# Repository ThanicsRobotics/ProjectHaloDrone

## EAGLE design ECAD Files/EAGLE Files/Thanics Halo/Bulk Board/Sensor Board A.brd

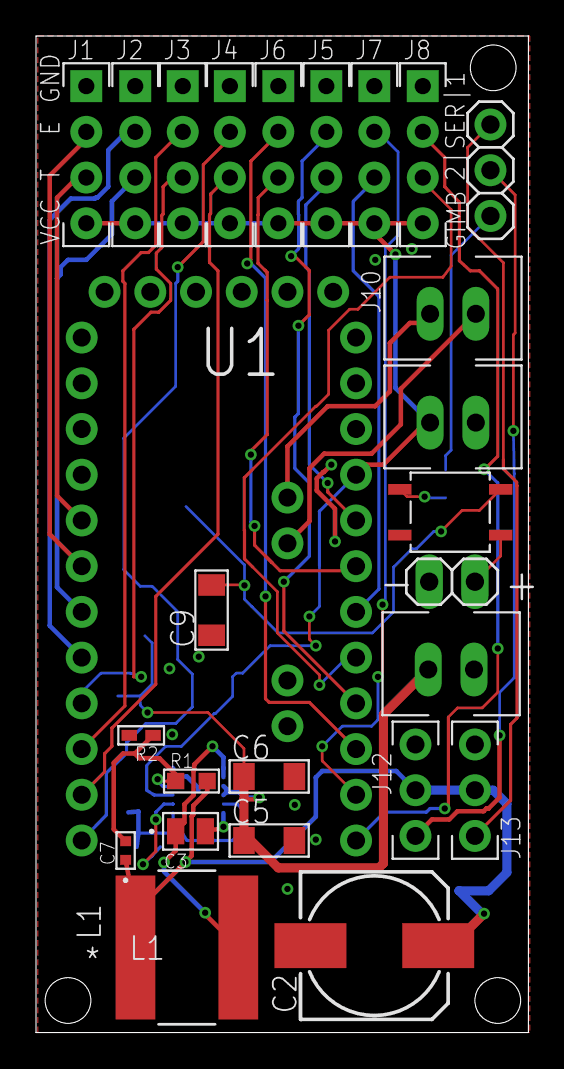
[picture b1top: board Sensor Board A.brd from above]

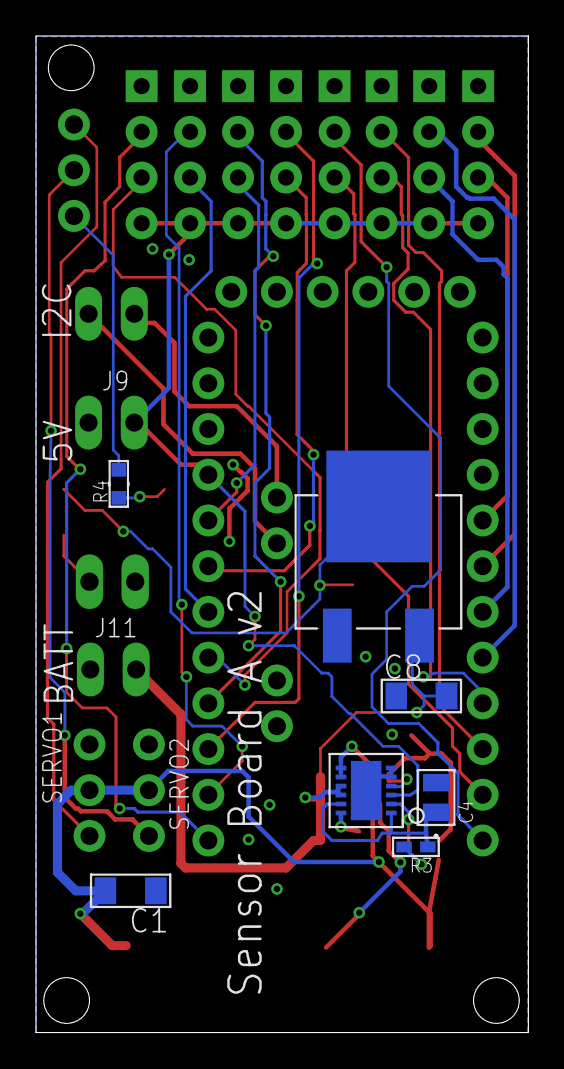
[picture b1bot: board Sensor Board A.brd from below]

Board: 2 copper layers, 27.4 x 55.4 mm, 33 parts (7 on the bottom side), 33 nets.

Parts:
C1, C5, C6, C8, C9: 10uF; 1206_MLCC
C2: 100uF; 0810_POLCAP
C3, C4: 0.1uF; 0805
C7: 16pF; G-155-M
J1, J2, J3, J4, J5, J6, J7, J8: HC-SR04; HC-SR04_FOOTPRINT
J9: POWER_CONNECTOR; XH_CONNECTOR
J10: I2C_CONNECTOR; XH_CONNECTOR
J11: GIMBAL_POWER_CONNECTOR; XH_CONNECTOR
J12, J13: SERVO_CONNECTOR
JP1: 1X03
JP2: 1X02
L1: 3.3uH; IND_BOURNS_SRN8040
R1: 499k; RC0603N-M
R2, R3: 95.3k; RC0402N-M
R4: 340R; RC0603N
U1: PRO-MINI-2
U2: 12LD4X3DFN
U3: 4-SOP
U4: DPAK

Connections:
+5V: J1.VCC, J2.VCC, J3.VCC, J4.VCC, J5.VCC, J6.VCC, J7.VCC, J8.VCC, J9.1, U1.VCC, U2.3
+12V: C9.P$2, U3.4, U4.2
ECHO1: J1.ECHO, U1.D3
ECHO2: J2.ECHO, U1.D5
ECHO3: J3.ECHO, U1.D7
ECHO4: J4.ECHO, U1.D9
ECHO5: J5.ECHO, U1.D13
ECHO6: J6.ECHO, U1.D12
ECHO7: J7.ECHO, U1.D11
ECHO8: J8.ECHO, U1.D10
GIMBAL: JP1.3, R4.2
GND: C1.P$1, C2.-, C4.2, C5.P$2, C6.P$2, C8.P$1, C9.P$1, J1.GND, J2.GND, J3.GND, J4.GND, J5.GND, J6.GND, J7.GND, J8.GND, J9.2, J11.2, J12.3, J13.3, JP2.2, R2.2, U1.GND, U1.GND1, U2.5, U2.6, U2.EP, U3.2, U4.1
unnamed: R4.1, U3.1
unnamed: R3.2, U2.2
unnamed: JP2.1, U3.3
unnamed: C7.2, R1.1, R2.1, U2.4
unnamed: C3.2, U2.12
unnamed: C3.1, L1.2, U2.7, U2.8
SCL: J10.1, U1.A5
SDA: J10.2, U1.A4
SERVO1: J12.1, JP1.1
SERVO2: J13.1, JP1.2
TRIG1: J1.TRIG, U1.D2
TRIG2: J2.TRIG, U1.D4
TRIG3: J3.TRIG, U1.D6
TRIG4: J4.TRIG, U1.D8
TRIG5: J5.TRIG, U1.A0
TRIG6: J6.TRIG, U1.A1
TRIG7: J7.TRIG, U1.A2
TRIG8: J8.TRIG, U1.A3
VDD: C4.1, R3.1, U2.1, U2.11
VOUT: C1.P$2, C2.+, C7.1, J12.2, J13.2, L1.1, R1.2
V_BATT: C5.P$1, C6.P$1, C8.P$2, J11.1, U2.9, U2.10, U4.3

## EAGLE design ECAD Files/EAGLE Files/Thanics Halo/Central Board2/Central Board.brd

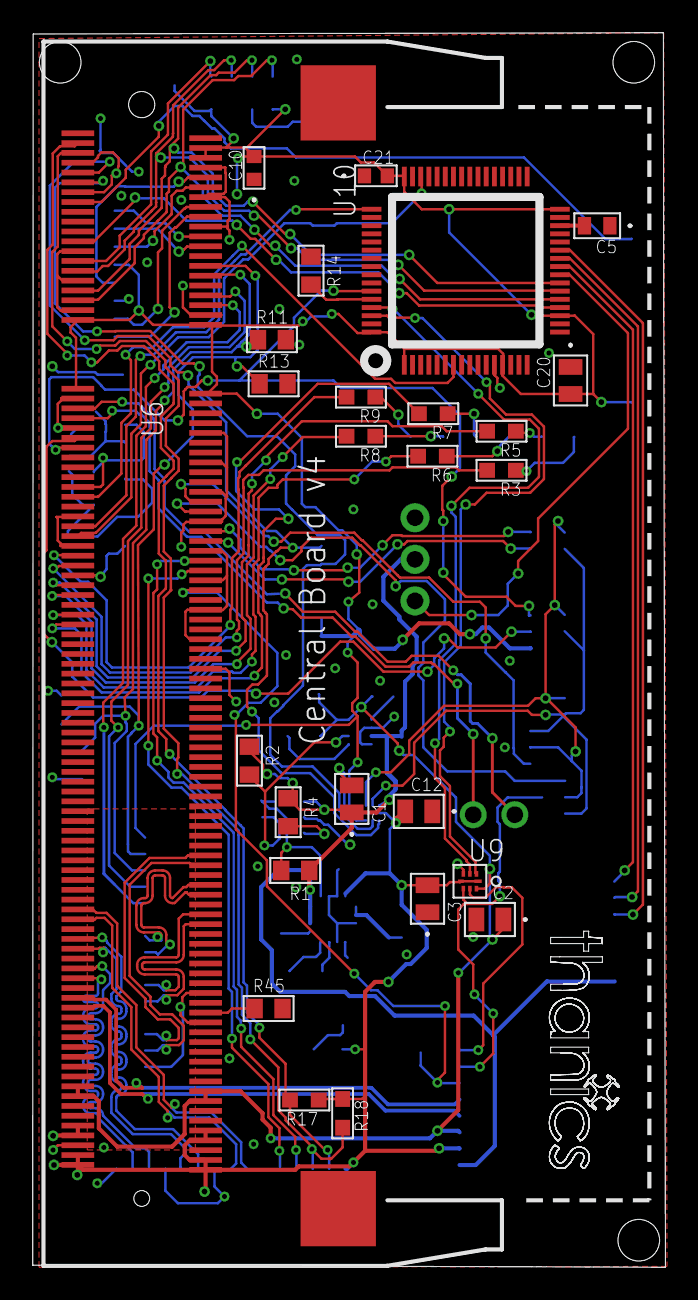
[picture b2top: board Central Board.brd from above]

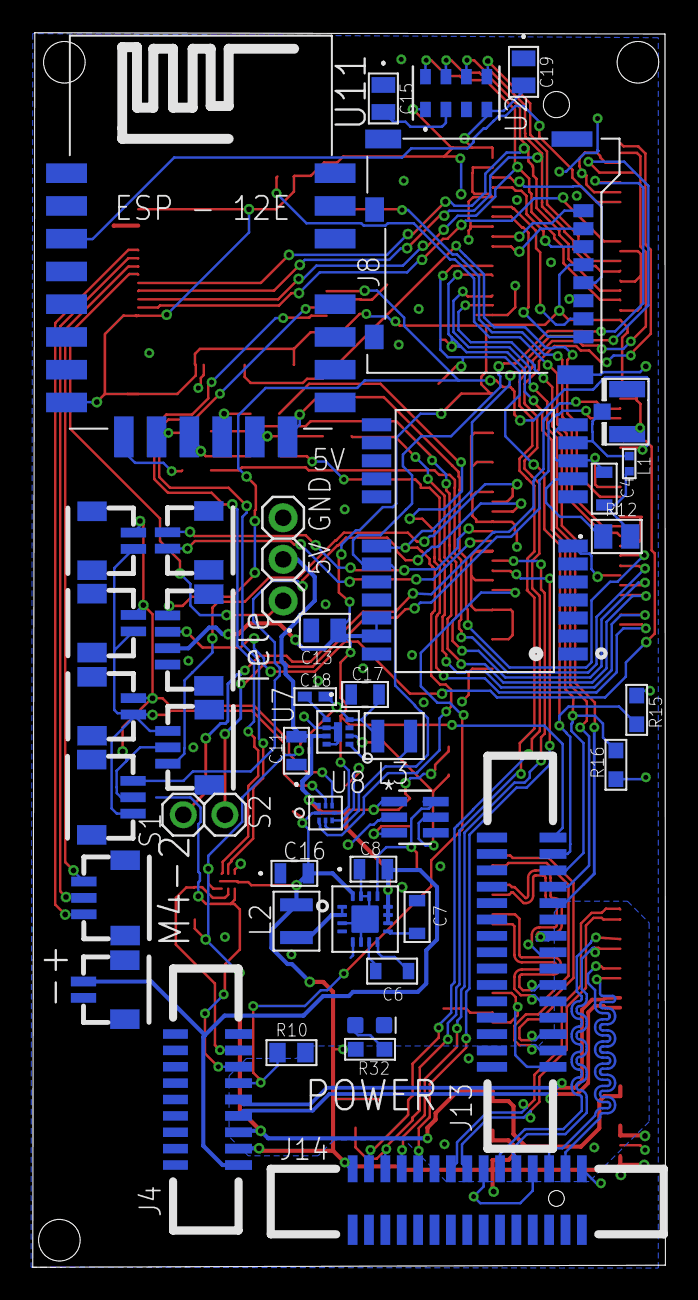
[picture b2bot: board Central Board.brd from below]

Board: 4 copper layers, 38.6 x 75.4 mm, 69 parts (43 on the bottom side), 91 nets.

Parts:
C1, C2, C3, C12, C13, C20: 0.1uF; 0805
C4, C6, C7: 10nF; 0603_CAPACITOR
C5: 4.7uF; 0603-M
C8, C11, C17: 10uF; G-21
C10, C21: 2.2uF; G-188-M
C15, C19: 1uF; YAG_CC0805
C16: 22uF; G-21
C18: 560pF; CC0402N-M
D1: GREEN; LED-0603
J1, J2, J6, J7, J9: JST_SH_2POS
J3: JST_SH_4POS
J4: 9POS_FFC_CONNECTOR
J5: U.FL
J8: MICROSD
J10, J11, J12: JST_SH_3POS
J13, J14: 15POS_FFC_CONNECTOR
JP1: 1X02
JP2: 1X03
L1: 27 nH; 0402_INDUCTOR
L2, L3: 470nH; 1008_INDUCTOR
R1, R2, R4, R10, R11, R13, R14, R45: 10k; RC0805N
R3, R5, R6, R7, R8, R9, R32: 20R; RC0603N-M
R12: 10; STA_RNCP0805-M
R15, R16, R17, R18: 1k; RC0603N-M
U2: LGA8-M
U3: LM3880MF-1AA/NOPBMF06A-M; MF06A-M
U4: NEO-M8
U5: TPS6209; VQFN16
U6: SO-DIMM
U7: MIC23050; MLF(ML)_8PIN
U8, U9: 8-UMLP
U10: LQFP64
U11: ESP12E-SMD

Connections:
1.8V: C2.1, C17.2, C18.2, J4.3, L3.P$2, U6.183, U6.184, U6.185, U6.186, U7.4, U9.8
+3V3: C3.2, C10.2, C12.2, C13.2, C16.2, C19.2, C20.2, C21.2, J3.3, J4.2, J8.4, J13.15, J14.15, L2.P$2, R15.1, R16.1, R17.1, R18.1, R32.2, U2.1, U2.4, U4.22, U4.23, U5.16, U6.4, U6.6, U6.39, U6.40, U6.41, U6.42, U6.191, U6.192, U6.193, U6.194, U6.197, U6.198, U6.199, U6.200, U8.1, U8.5, U9.1, U9.5, U10.1, U10.13, U10.19, U10.32, U10.48, U10.64, U11.VCC
+5V: C1.1, C8.2, C11.2, J4.1, J6.1, JP2.2, R1.1, R2.1, R4.1, U3.1, U5.10, U5.11, U5.12, U7.7, U8.8
C0_C_N: J13.8, U6.144
C0_C_P: J13.9, U6.142
C0_D0_N: J13.2, U6.138
C0_D0_P: J13.3, U6.136
C0_D1_N: J13.5, U6.150
C0_D1_P: J13.6, U6.148
C0_IO0: J13.11, U6.36
C0_IO1: J13.12, U6.34
C1_C_N: J14.8, U6.149
C1_C_P: J14.9, U6.147
C1_D0_N: J14.2, U6.161
C1_D0_P: J14.3, U6.159
C1_D1_N: J14.5, U6.155
C1_D1_P: J14.6, U6.153
C1_IO0: J14.11, U6.78
C1_IO1: J14.12, U6.76
GND: C1.2, C2.2, C3.1, C4.1, C5.1, C7.1, C8.1, C10.1, C11.1, C12.1, C13.1, C15.1, C16.1, C17.1, C19.1, C20.1, C21.1, D1.C, J3.4, J4.9, J5.P$1, J5.P$2, J6.2, J8.6, J8.9, J8.10, J8.11, J8.12, J8.13, J13.1, J13.4, J13.7, J13.10, J14.1, J14.4, J14.7, J14.10, JP2.3, R10.2, R11.2, R13.2, R14.1, R45.2, U2.3, U3.2, U4.7, U4.10, U4.12, U4.13, U4.24, U5.3, U5.5, U5.6, U5.14, U5.15, U5.17, U6.1, U6.7, U6.8, U6.13, U6.14, U6.19, U6.20, U6.25, U6.26, U6.31, U6.32, U6.37, U6.38, U6.43, U6.44, U6.49, U6.50, U6.55, U6.56, U6.61, U6.62, U6.67, U6.68, U6.73, U6.74, U6.79, U6.80, U6.85, U6.86, U6.91, U6.92, U6.97, U6.98, U6.103, U6.104, U6.109, U6.110, U6.115, U6.116, U6.121, U6.122, U6.127, U6.133, U6.134, U6.139, U6.140, U6.145, U6.146, U6.151, U6.152, U6.157, U6.163, U6.164, U6.169, U6.170, U6.181, U6.182, U6.187, U6.188, U6.195, U6.196, U6.G1, U6.G2, U7.6, U7.8, U7.EP, U8.4, U9.4, U10.12, U10.18, U10.31, U10.47, U10.63, U11.GND
GPCLK1: J4.6, R10.1, U6.82
I2C_MPU_SCL: U9.3, U10.61
I2C_MPU_SDA: U9.2, U10.62
I2C_SCL: U4.19, U6.11, U8.3
I2C_SCL_1V8: J4.7, U9.6
I2C_SCL_5V: J1.2, J2.2, J7.2, J10.2, J11.2, U8.6
I2C_SDA: U4.18, U6.9, U8.2
I2C_SDA_1V8: J4.8, U9.7
I2C_SDA_5V: J1.1, J2.1, J7.1, J10.1, J11.1, U8.7
ID_SD: U6.15, U11.CH_PD
INT_A: J10.3, U6.64
INT_B: J11.3, U6.66
MOTOR1: JP2.1, U10.24
MOTOR2: J12.1, U10.25
MOTOR3: J12.2, U10.26
MOTOR4: J12.3, U10.27
unnamed: J5.P$3, L1.P$1, U4.11
unnamed: C6.2, U5.7
unnamed: C6.1, U5.8
unnamed: D1.A, R32.1
unnamed: R1.2, U3.6, U5.13
unnamed: R2.2, U3.5, U7.2
unnamed: R3.1, U11.CS0
unnamed: R5.1, U11.MISO
unnamed: R6.1, U11.GPIO9
unnamed: R7.1, U11.GPIO10
unnamed: C5.2, U10.30
unnamed: C15.2, U2.2
unnamed: R12.1, U4.9
unnamed: R8.1, U11.MOSI
unnamed: R9.1, U11.SCLK
unnamed: R14.2, U10.60
unnamed: C4.2, L1.P$2, R12.2
unnamed: C7.2, U5.9
unnamed: L2.P$1, U5.1, U5.2
unnamed: L3.P$1, U7.1
unnamed: C18.1, U7.5
unnamed: R45.1, U6.168
NRST: U6.63, U10.7
POWER_SEQ_EN: R4.2, U3.3
SCL0: J13.13, R11.1, R16.2, U6.30
SCL1: J14.13, R18.2, U6.5
SDA0: J13.14, R13.1, R15.2, U6.28
SDA1: J14.14, R17.2, U6.3
SDX_CLK: J8.5, U6.10
SDX_CMD: J8.3, U6.12
SDX_D0: J8.7, U6.16
SDX_D1: J8.8, U6.18
SDX_D2: J8.1, U6.22
SDX_D3: J8.2, U6.24
SD_CLK: R9.2, U6.75
SD_CMD: R3.2, U6.77
SD_D0: R5.2, U6.81
SD_D1: R8.2, U6.83
SD_D2: R6.2, U6.87
SD_D3: R7.2, U6.89
SERVO1: JP1.1, U6.45
SERVO2: JP1.2, U6.47
SPI_CS0: U2.5, U6.27
SPI_CS1: U6.23, U10.20
SPI_MISO: U2.6, U6.29, U10.22
SPI_MOSI: U2.7, U6.33, U10.23
SPI_SCLK: U2.8, U6.35, U10.21
SWCLK: U6.69, U10.49
SWDIO: U6.71, U10.46
UART2_RX: J9.2, U6.72
UART2_TX: J9.1, U6.70
USART1_RX: J3.1, U6.53, U10.59
USART1_TX: J3.2, U6.51
USB_D_N: J4.4, U6.167
USB_D_P: J4.5, U6.165

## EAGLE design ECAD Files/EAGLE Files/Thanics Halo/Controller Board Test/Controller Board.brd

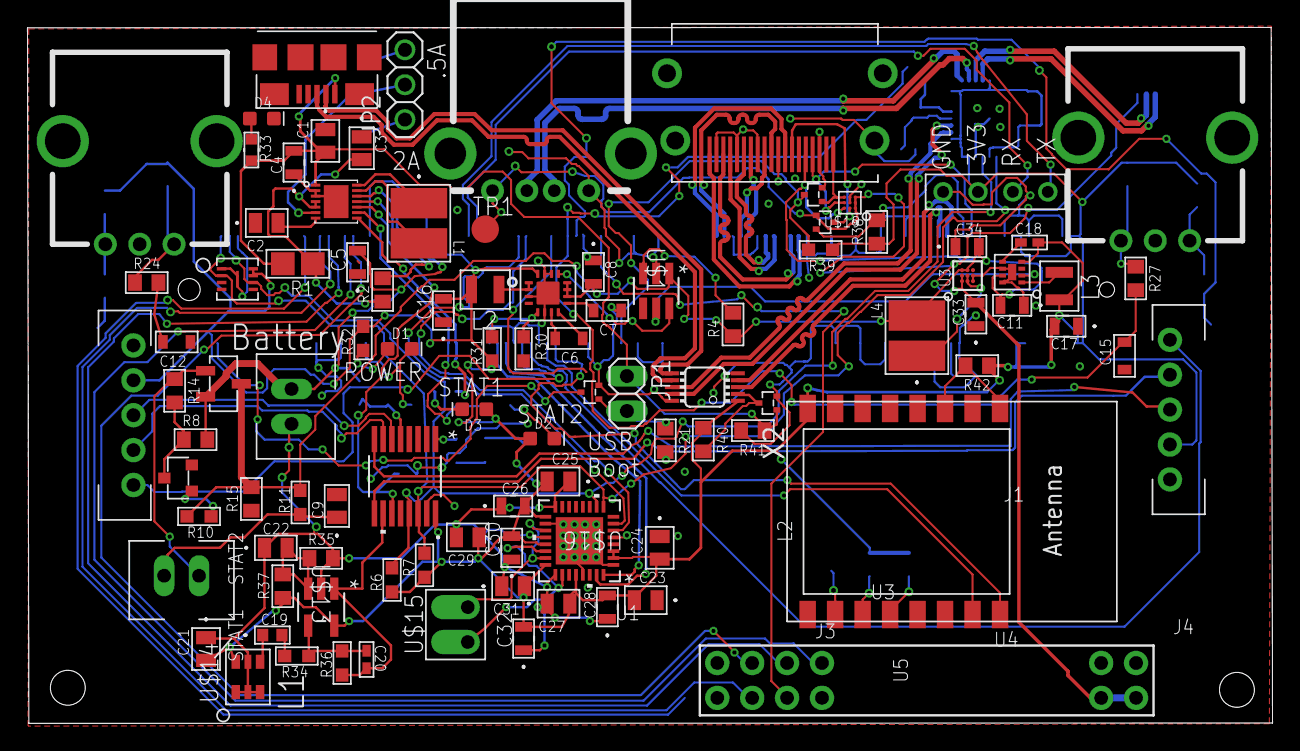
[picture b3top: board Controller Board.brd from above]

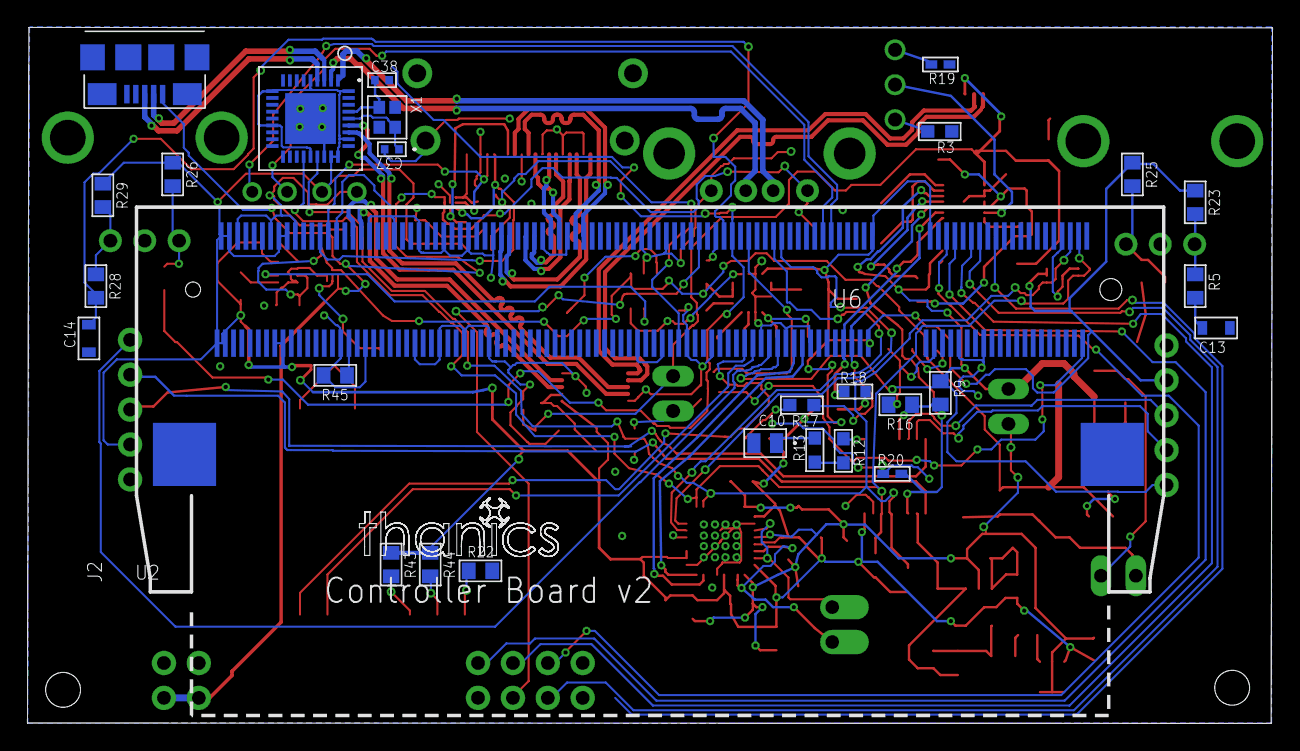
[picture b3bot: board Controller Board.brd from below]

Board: 2 copper layers, 90.6 x 50.6 mm, 128 parts (28 on the bottom side), 113 nets.

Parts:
C1, C2, C10, C21, C23, C24, C25, C27, C29, C31: 0.1uF; 0805
C3, C9, C22: 1uF; YAG_CC0805
C4, C8, C11, C17, C26, C28, C33, C34: 10uF; G-21
C5, C16, C30, C32: 22uF; G-21
C6, C7, C12, C13, C14, C15: 10nF; 0603_CAPACITOR
C18, C20: 560pF; CC0402N-M
C19: 2.2uF; G-188-M
C37, C38: 16pF; G-155-M
D1, D2, D3, D4: GREEN; LED-0603
IC1: FSUSB42MSOP10; MSOP10
J1, J2: JOYSTICK; JST-XH_5POS
J3, J5: USB_MICRO_B_SMT
J4: 2_PIN_CONNECTOR; XH_CONNECTOR
J6: POWER_CONNECTOR; XH_CONNECTOR
J7: HDMI
JP1: 1X02
JP2: 1X03
L1, L4: 4.7uH; IND_IFSC_1515AH-M
L2, L3: 470nH; 470NH_INDUCTOR
R1: 100; 1206
R2, R4, R5, R8, R9, R14, R15, R16, R21, R22, R23, R24, R25, R26, R27, R28, R29, R35, R37, R40, R41, R42, R43, R44, R45: 10k; RC0805N
R3, R10, R36, R39: 100k; RC0603N-M
R6, R7, R12, R13, R34: 1k; RC0603N-M
R11: 1M; RC0603N-M
R17, R32: 20R; RC0603N-M
R18, R33: 340R; RC0603N
R19, R20: 24.9k; RC0402N-M
R30: 160k; RC0603N-M
R31: 499k; RC0603N-M
R38: NF; RC0805N
TP1: TPSQTP20R; TP20R
U1: AAT3620_BATT_CHARGER; AAT3620_TDFN
U2: 8 CH; 21-0055H_16-M
U3: YFF9
U4: DMP3030SN_MOSFET; SC59_MOSFET
U5: SOT-23_(TO-236AB)
U6: COMPUTE_MODULE; SO-DIMM
U$1: LM3880MF-1AA/NOPBMF06A-M; MF06A-M
U$2: APPLE_2.0C_COPROCESSOR; PG-USON-8-1
U$3: 4_PIN_TELE_CONNECTOR
U$4: MIC23050; MLF(ML)_8PIN
U$5: TPS6209; VQFN16
U$9, U$10: PEC12R
U$11: USB_A_RECEPT
U$12: 3.5_TOUCHSCREEN
U$13: SOT-23-5_MC-M
U$14: SISONIC_MICROPHONE
U$15: SPEAKER
U$16: RHB32_3P45X3P45
U$18, U$20, U$21, U$23: SOT-523
U$19: ESD5384; WLCSP9
U$24: 36-SQFN
U$25: AGND-DGND
X1: 24MHZ; FA-128
X2: ESP-12

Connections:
+3V3: C16.2, C17.2, C18.2, C21.2, C23.2, C24.2, C25.2, C26.2, C27.2, C28.2, C29.2, C30.2, C31.2, C32.2, D2.A, D3.A, IC1.1, J1.2, J2.2, L2.P$2, L3.P$2, R6.1, R7.1, R23.1, R25.1, R26.1, R29.1, R31.1, R32.2, R37.1, R38.1, R39.1, R40.1, R42.1, R43.1, R44.1, U2.16, U6.39, U6.40, U6.41, U6.42, U6.183, U6.184, U6.185, U6.186, U6.197, U6.198, U6.199, U6.200, U$2.7, U$2.8, U$3.3, U$4.4, U$5.16, U$13.5, U$14.6, U$16.2, U$16.3, U$16.17, U$16.21, U$16.24, U$16.28, U$24.5, U$24.10, U$24.15, U$24.23, U$24.26, U$24.27, U$24.29, U$24.36, X2.8
+5V: C33.2, J5.1, TP1.TP, U3.A1, U3.A2, U$11.1, U$12.1, U$12.2, U$18.G, U$19.A1, U$19.B1, U$19.C1
AGND: C21.1, C22.1, C25.1, C26.1, C27.1, C28.1, C29.1, C30.1, C31.1, C32.1, R35.2, U$13.2, U$14.1, U$14.2, U$14.3, U$14.5, U$16.16, U$16.20, U$16.25, U$25.1
D1_N: IC1.6, J3.2
D1_P: IC1.7, J3.3
D2_N: IC1.8, U$24.30
D2_P: IC1.9, U$24.31
DS1_N: U$11.2, U$24.1
DS1_P: U$11.3, U$24.2
DS2_N: J5.2, U$24.3
DS2_P: J5.3, U$24.4
EMMC_DISABLE_N: U6.2, U$20.D
ENCODER1_A: C13.2, R5.2, U6.76
ENCODER1_B: C12.2, R24.2, U6.78
ENCODER2_A: C15.2, R27.2, U6.75
ENCODER2_B: C14.2, R28.2, U6.77
GND: C1.1, C2.1, C3.1, C4.1, C5.1, C7.1, C8.1, C9.2, C10.2, C11.1, C12.1, C13.1, C14.1, C15.1, C16.1, C17.1, C23.1, C24.1, C33.1, C34.1, C37.2, C38.2, D1.C, D4.C, IC1.5, IC1.10, J1.1, J2.1, J3.4, J3.5, J3.6, J3.7, J3.P$1, J3.P$2, J3.P$3, J3.P$4, J5.4, J5.5, J5.6, J5.7, J5.P$1, J5.P$2, J5.P$3, J5.P$4, J6.2, J7.2, J7.5, J7.8, J7.11, J7.17, J7.P$1, J7.P$2, J7.P$3, J7.P$4, R3.1, R15.1, R16.2, R19.1, R20.1, R21.2, R22.2, R30.2, R41.2, R45.2, U1.2, U1.3, U1.EP, U2.15, U3.C1, U3.C2, U5.S, U6.1, U6.7, U6.8, U6.13, U6.14, U6.19, U6.20, U6.25, U6.26, U6.31, U6.32, U6.37, U6.38, U6.43, U6.44, U6.49, U6.50, U6.55, U6.56, U6.61, U6.62, U6.67, U6.68, U6.73, U6.74, U6.79, U6.80, U6.85, U6.86, U6.91, U6.92, U6.97, U6.98, U6.103, U6.104, U6.109, U6.110, U6.115, U6.116, U6.121, U6.122, U6.127, U6.133, U6.134, U6.139, U6.140, U6.145, U6.146, U6.151, U6.152, U6.157, U6.163, U6.164, U6.169, U6.170, U6.181, U6.182, U6.187, U6.188, U6.195, U6.196, U6.G1, U6.G2, U$1.2, U$2.1, U$2.9, U$3.4, U$4.6, U$4.8, U$4.EP, U$5.3, U$5.6, U$5.14, U$5.15, U$5.17, U$9.C, U$10.C, U$11.4, U$11.5, U$11.6, U$12.3, U$12.7, U$16.1, U$16.18, U$16.29, U$16.33, U$19.B2, U$19.C2, U$20.S, U$21.S, U$23.S, U$24.25, U$24.EP, U$25.2, X2.9
GPIO18: U6.63, U$16.7
GPIO19: U6.65, U$16.6
GPIO21: U6.71, U$16.5
GPIO25: U6.83, U$12.4
GPIO36: U6.58, U$16.32
GPIO37: U6.60, U$16.31
HDMI_CEC: R38.2, U6.171, U$18.S
HDMI_CK_N: J7.12, U6.111
HDMI_CK_P: J7.10, U6.113
HDMI_D0_N: J7.9, U6.117
HDMI_D0_P: J7.7, U6.119
HDMI_D1_N: J7.6, U6.123
HDMI_D1_P: J7.4, U6.125
HDMI_D2_N: J7.3, U6.129
HDMI_D2_P: J7.1, U6.131
HDMI_HPD_N_1V8: R39.2, U6.88, U$21.D
HDMI_SCL: J7.15, U6.175, U$19.A3
HDMI_SDA: J7.16, U6.173, U$19.B3
I2C_SCL: R6.2, U2.13, U6.5, U$2.6, U$16.10, U$24.24
I2C_SDA: R7.2, U2.14, U6.3, U$2.2, U$16.9, U$24.22
ISET: JP2.2, U1.6
ITERM: R20.2, U1.10, U2.11
J1_SW: J1.5, U6.64
J2_SW: J2.5, U6.66
MIC_OUTPUT: C20.2, R36.1, U2.10, U$13.1
unnamed: J4.1, R14.1, U4.G
unnamed: C2.2, U1.7
unnamed: JP1.2, R21.1, U$20.G
unnamed: L1.2, U1.13
unnamed: L1.1, U1.14
unnamed: C3.2, R1.1, R2.1, U1.4, U1.5
unnamed: C5.2, J6.1, R8.2, R9.1, U1.12, U4.S
unnamed: U$1.6, U$5.13
unnamed: D4.A, R33.1
unnamed: D1.A, R32.1
unnamed: R2.2, U1.11
unnamed: U$1.5, U$4.2
unnamed: C6.2, U$5.7
unnamed: C19.1, U$14.4
unnamed: D2.C, R17.2
unnamed: R12.1, U2.1
unnamed: J1.3, U2.6
unnamed: J1.4, U2.7
unnamed: J2.3, U2.8
unnamed: J2.4, U2.9
unnamed: C19.2, R34.2
unnamed: D3.C, R18.2
unnamed: C6.1, U$5.8
unnamed: R12.2, R13.1
unnamed: R10.1, U5.G
unnamed: C9.1, J4.2, R11.1
unnamed: R8.1, R14.2, U5.D
unnamed: C10.1, R13.2
unnamed: C7.2, U$5.9
unnamed: L2.P$1, U$5.1, U$5.2
unnamed: R5.1, R23.2, U$9.A
unnamed: L3.P$1, U$4.1
unnamed: R42.2, X2.1, X2.3
unnamed: R24.1, R25.2, U$9.B
unnamed: C20.1, R34.1, R36.2, U$13.4
unnamed: C22.2, R35.1, R37.2, U$13.3
unnamed: R26.2, R27.1, U$10.A
unnamed: R28.1, R29.2, U$10.B
unnamed: R9.2, R16.1, U2.5
unnamed: JP2.1, R3.2
unnamed: U$15.1, U$16.22, U$16.26
unnamed: JP2.3, R19.2
unnamed: R22.1, X2.10
unnamed: U$15.2, U$16.19, U$16.23
unnamed: R43.2, X2.12
unnamed: R30.1, R31.2, U$5.5
unnamed: C8.2, C11.2, C34.2, L4.2, R4.1, R10.2, R11.2, R15.2, U3.A3, U3.B3, U4.D, U$1.1, U$4.7, U$5.10, U$5.11, U$5.12
unnamed: C18.1, U$4.5
unnamed: J7.13, U$18.D, U$19.A2
unnamed: J7.19, U$19.C3, U$21.G
unnamed: R44.2, X2.11
unnamed: C38.1, U$24.33, X1.1
unnamed: R45.1, U6.168
unnamed: IC1.2, R40.2, U$23.D
unnamed: C37.1, U$24.32, X1.3
unnamed: L4.1, U3.B1, U3.B2
POWER_SEQ_EN: R4.2, U$1.3
SPI_CS0: U6.27, U$12.5
SPI_CS1: U6.23, U$12.6
SPI_MISO: U6.29, U$12.9
SPI_MOSI: U6.33, U$12.10
SPI_SCLK: U6.35, U$12.8
STAT1: R17.1, U1.9, U6.46
STAT2: R18.1, U1.8, U6.48
UART2_RX: U6.72, X2.16
UART2_TX: U6.70, X2.15
UART_RX: U6.53, U$3.2
UART_TX: U6.51, U$3.1
USB_5V: C1.2, C4.2, J3.1, JP1.1, R1.2, R33.2, R41.1, U1.1, U$23.G
USB_D_N: IC1.4, U6.167
USB_D_P: IC1.3, U6.165

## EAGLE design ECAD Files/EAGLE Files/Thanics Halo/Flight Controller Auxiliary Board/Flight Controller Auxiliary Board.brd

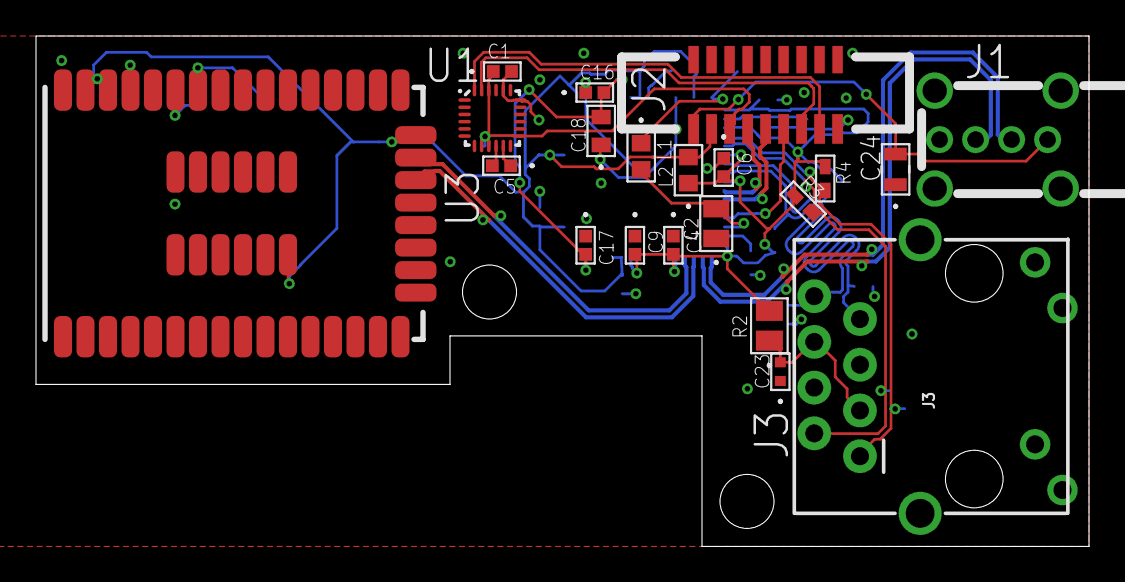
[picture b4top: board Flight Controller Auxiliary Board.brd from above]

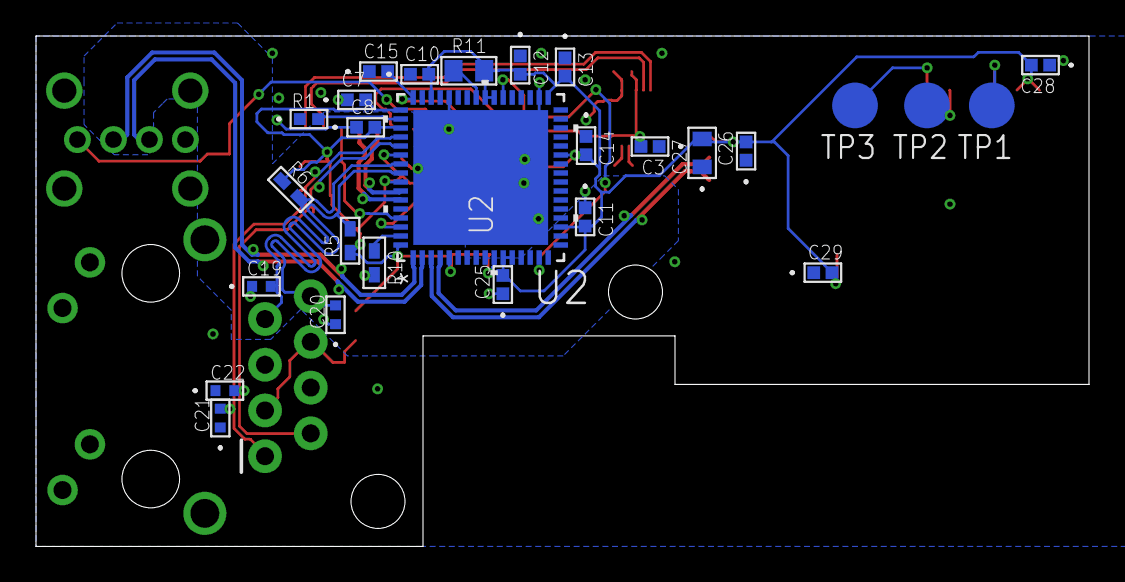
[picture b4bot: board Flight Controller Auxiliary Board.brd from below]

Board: 4 copper layers, 58.5 x 28.4 mm, 48 parts (27 on the bottom side), 29 nets.

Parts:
C1, C3, C4, C5, C6, C7, C8, C9, C10, C11, C12, C13, C14, C15, C16, C17, C25, C26, C28, C29: 0.1uF; 0402-M
C2: 1uF; YAG_CC0805
C18, C27: 4.7uF; 0603-M
C19, C20, C21, C22: 16pF; G-155-M
C23: 22nF; G-155-M
C24: 22uF; G-21
J1: USB_A_VERTICAL
J2: 9POS_FFC_CONNECTOR
J3: MAGJACK
L1, L2: FB; IND_BLM18_0603-M
R1: 12.4k; YAG_R0402-M
R2: 10R; STA_RNCP0805-M
R3, R4, R5, R6: 49R9; RC0402N-M
R10: 12k; RC0402N-M
R11: 10k; RC0805N
TP1, TP2, TP3: TPB2,54; B2,54
U1: QFN40P300X300X105-25N
U2: QFN64_9X9MC-M
U3: WGM110A

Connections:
1.8V: C1.1, C3.2, J2.3, U1.8, U1.9, U1.13, U1.22
3.3V_A: C4.2, C6.2, C7.2, C8.2, C9.2, L2.1, R2.2, R3.1, R4.1, R5.1, R6.1, U2.5, U2.10, U2.49, U2.51, U2.54, U2.57, U2.64
+3V3: C10.2, C11.2, C12.2, C13.2, C14.2, C25.2, C26.2, C27.2, C28.2, C29.2, J2.2, L2.2, R11.2, U2.11, U2.12, U2.19, U2.27, U2.33, U2.39, U2.40, U2.46, U3.24, U3.38, U3.39, U3.51
+5V: C24.2, J1.1, J2.1
GND: C1.2, C2.1, C3.1, C4.1, C5.1, C6.1, C7.1, C8.1, C9.1, C10.1, C11.1, C12.1, C13.1, C14.1, C15.1, C16.1, C17.1, C18.1, C19.1, C20.1, C21.1, C22.1, C23.1, C24.1, C25.1, C26.1, C27.1, C28.1, C29.1, J1.4, J1.P$5, J1.P$6, J1.P$7, J1.P$8, J2.9, J3.10, J3.12, J3.M1, J3.M2, R1.1, R10.2, U1.11, U1.18, U1.20, U2.34, U2.44, U2.65, U3.1, U3.16, U3.25, U3.40, U3.42, U3.44, U3.46, U3.48
GPCLK: J2.6, U2.61
unnamed: R11.1, U2.41
unnamed: R10.1, U2.63
unnamed: C15.2, L1.1, U2.48
unnamed: C2.2, L1.2, U2.62
unnamed: TP1.TP, U3.37
unnamed: TP2.TP, U3.35
unnamed: TP3.TP, U3.34
unnamed: C5.2, U1.10
unnamed: R1.2, U2.50
unnamed: C16.2, C17.2, C18.2, U2.15, U2.38
unnamed: C23.2, J3.3, J3.6, R2.1
RX_N: C22.2, J3.2, R3.2, U2.53
RX_P: C21.2, J3.1, R4.2, U2.52
SCL: J2.7, U1.23
SDA: J2.8, U1.24
TX_N: C20.2, J3.8, R5.2, U2.56
TX_P: C19.2, J3.7, R6.2, U2.55
USB_D2_N: J1.2, U2.1
USB_D2_P: J1.3, U2.2
USB_D3_N: U2.3, U3.22
USB_D3_P: U2.4, U3.23
USB_D_N: J2.4, U2.58
USB_D_P: J2.5, U2.59

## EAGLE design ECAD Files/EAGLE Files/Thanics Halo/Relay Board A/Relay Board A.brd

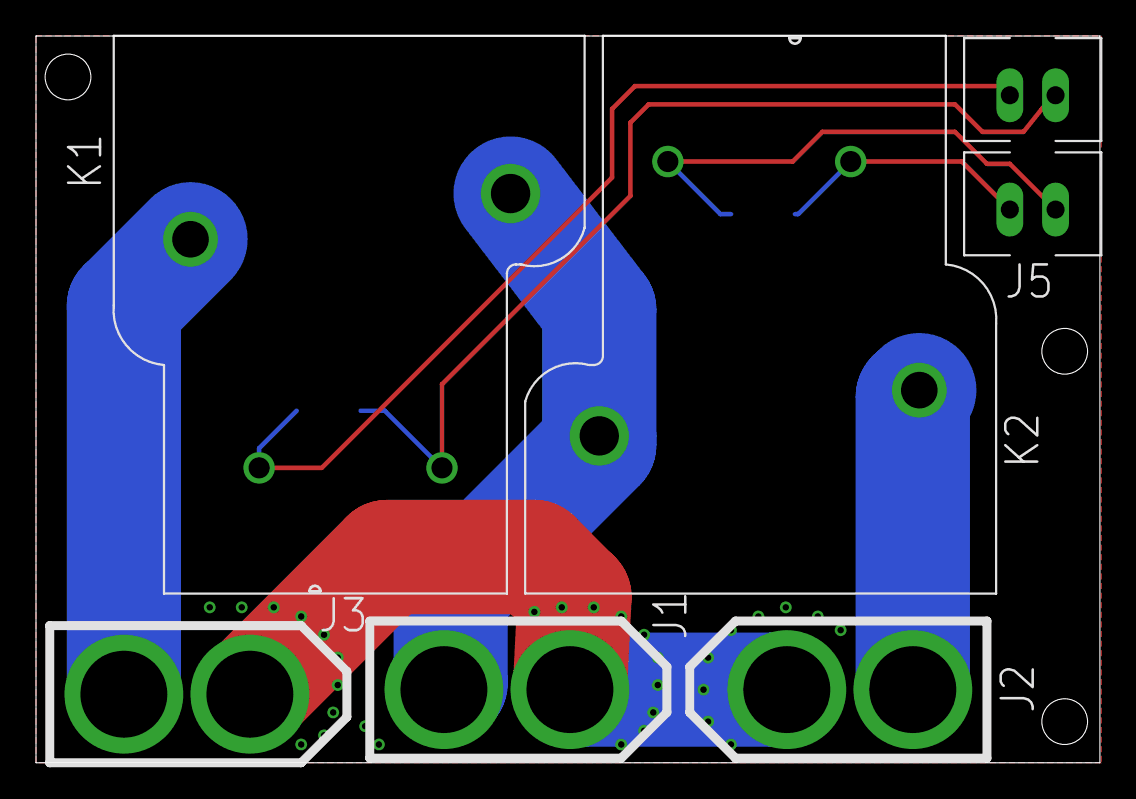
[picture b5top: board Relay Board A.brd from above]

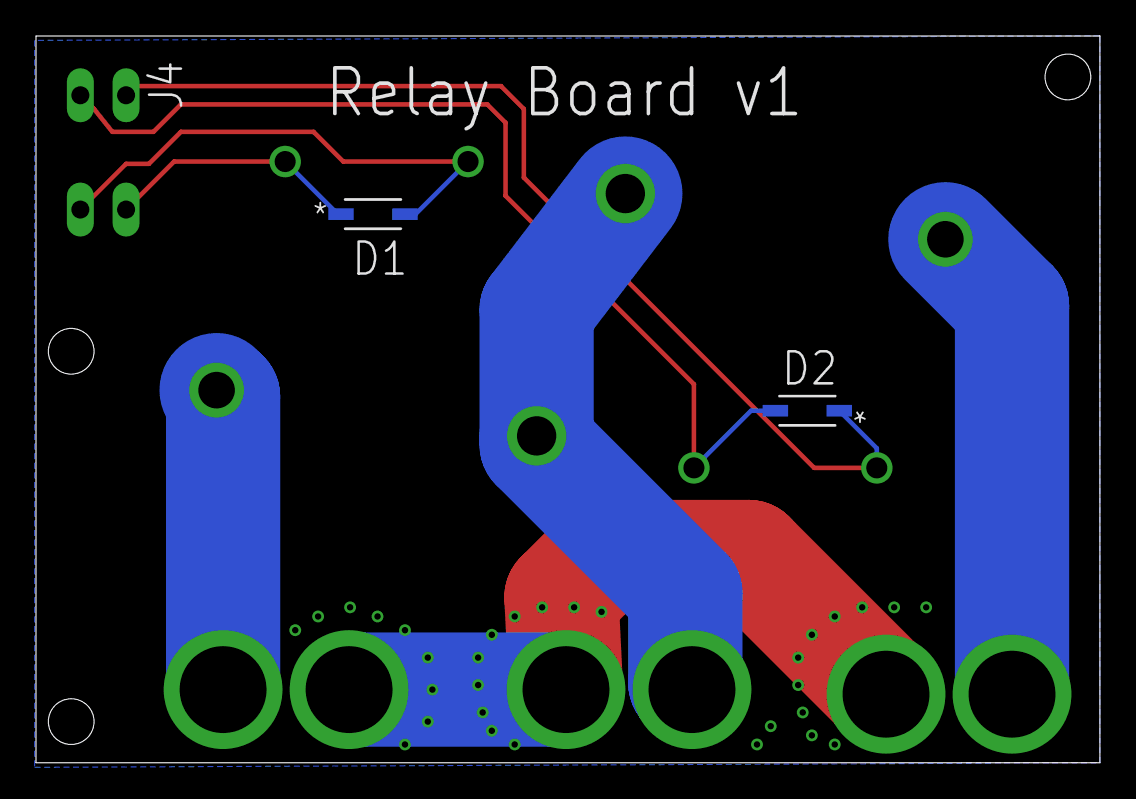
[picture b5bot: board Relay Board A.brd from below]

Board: 2 copper layers, 59.1 x 40.4 mm, 9 parts (2 on the bottom side), 8 nets.

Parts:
D1, D2: SOD123-M
J1, J2, J3: ESC_CONTACTS; XT60_CONNECTOR
J4, J5: POWER_CONNECTOR; XH_CONNECTOR
K1, K2: RELAY_T9AS

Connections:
GND: J1.-, J2.-, J3.-
unnamed: J1.+, K1.6, K2.6
unnamed: J2.+, K1.3
unnamed: J3.+, K2.3
unnamed: D1.C, J5.1, K1.2
unnamed: D1.A, J5.2, K1.7
unnamed: D2.C, J4.1, K2.2
unnamed: D2.A, J4.2, K2.7

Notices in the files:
parts and their libraries:
COPYRIGHT: Copyright C 2015 Accelerated Designs. All rights reserved
SparkFun-Connectors: Licensing: Creative Commons ShareAlike 4.0 International - https://creativecommons.org/licenses/by-sa/4.0
